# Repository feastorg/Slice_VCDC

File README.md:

# Current & Voltage Reader Slice

Current and voltage reader slice for AC and DC supplies.

## Introduction

[Short introduction on the project.]

## Usage

[Explain how to use the project. Include examples and screenshots if applicable.]

## Documentation

Please refer to the [docs](/docs) for more info.

---

<div align="center">
  
</div>

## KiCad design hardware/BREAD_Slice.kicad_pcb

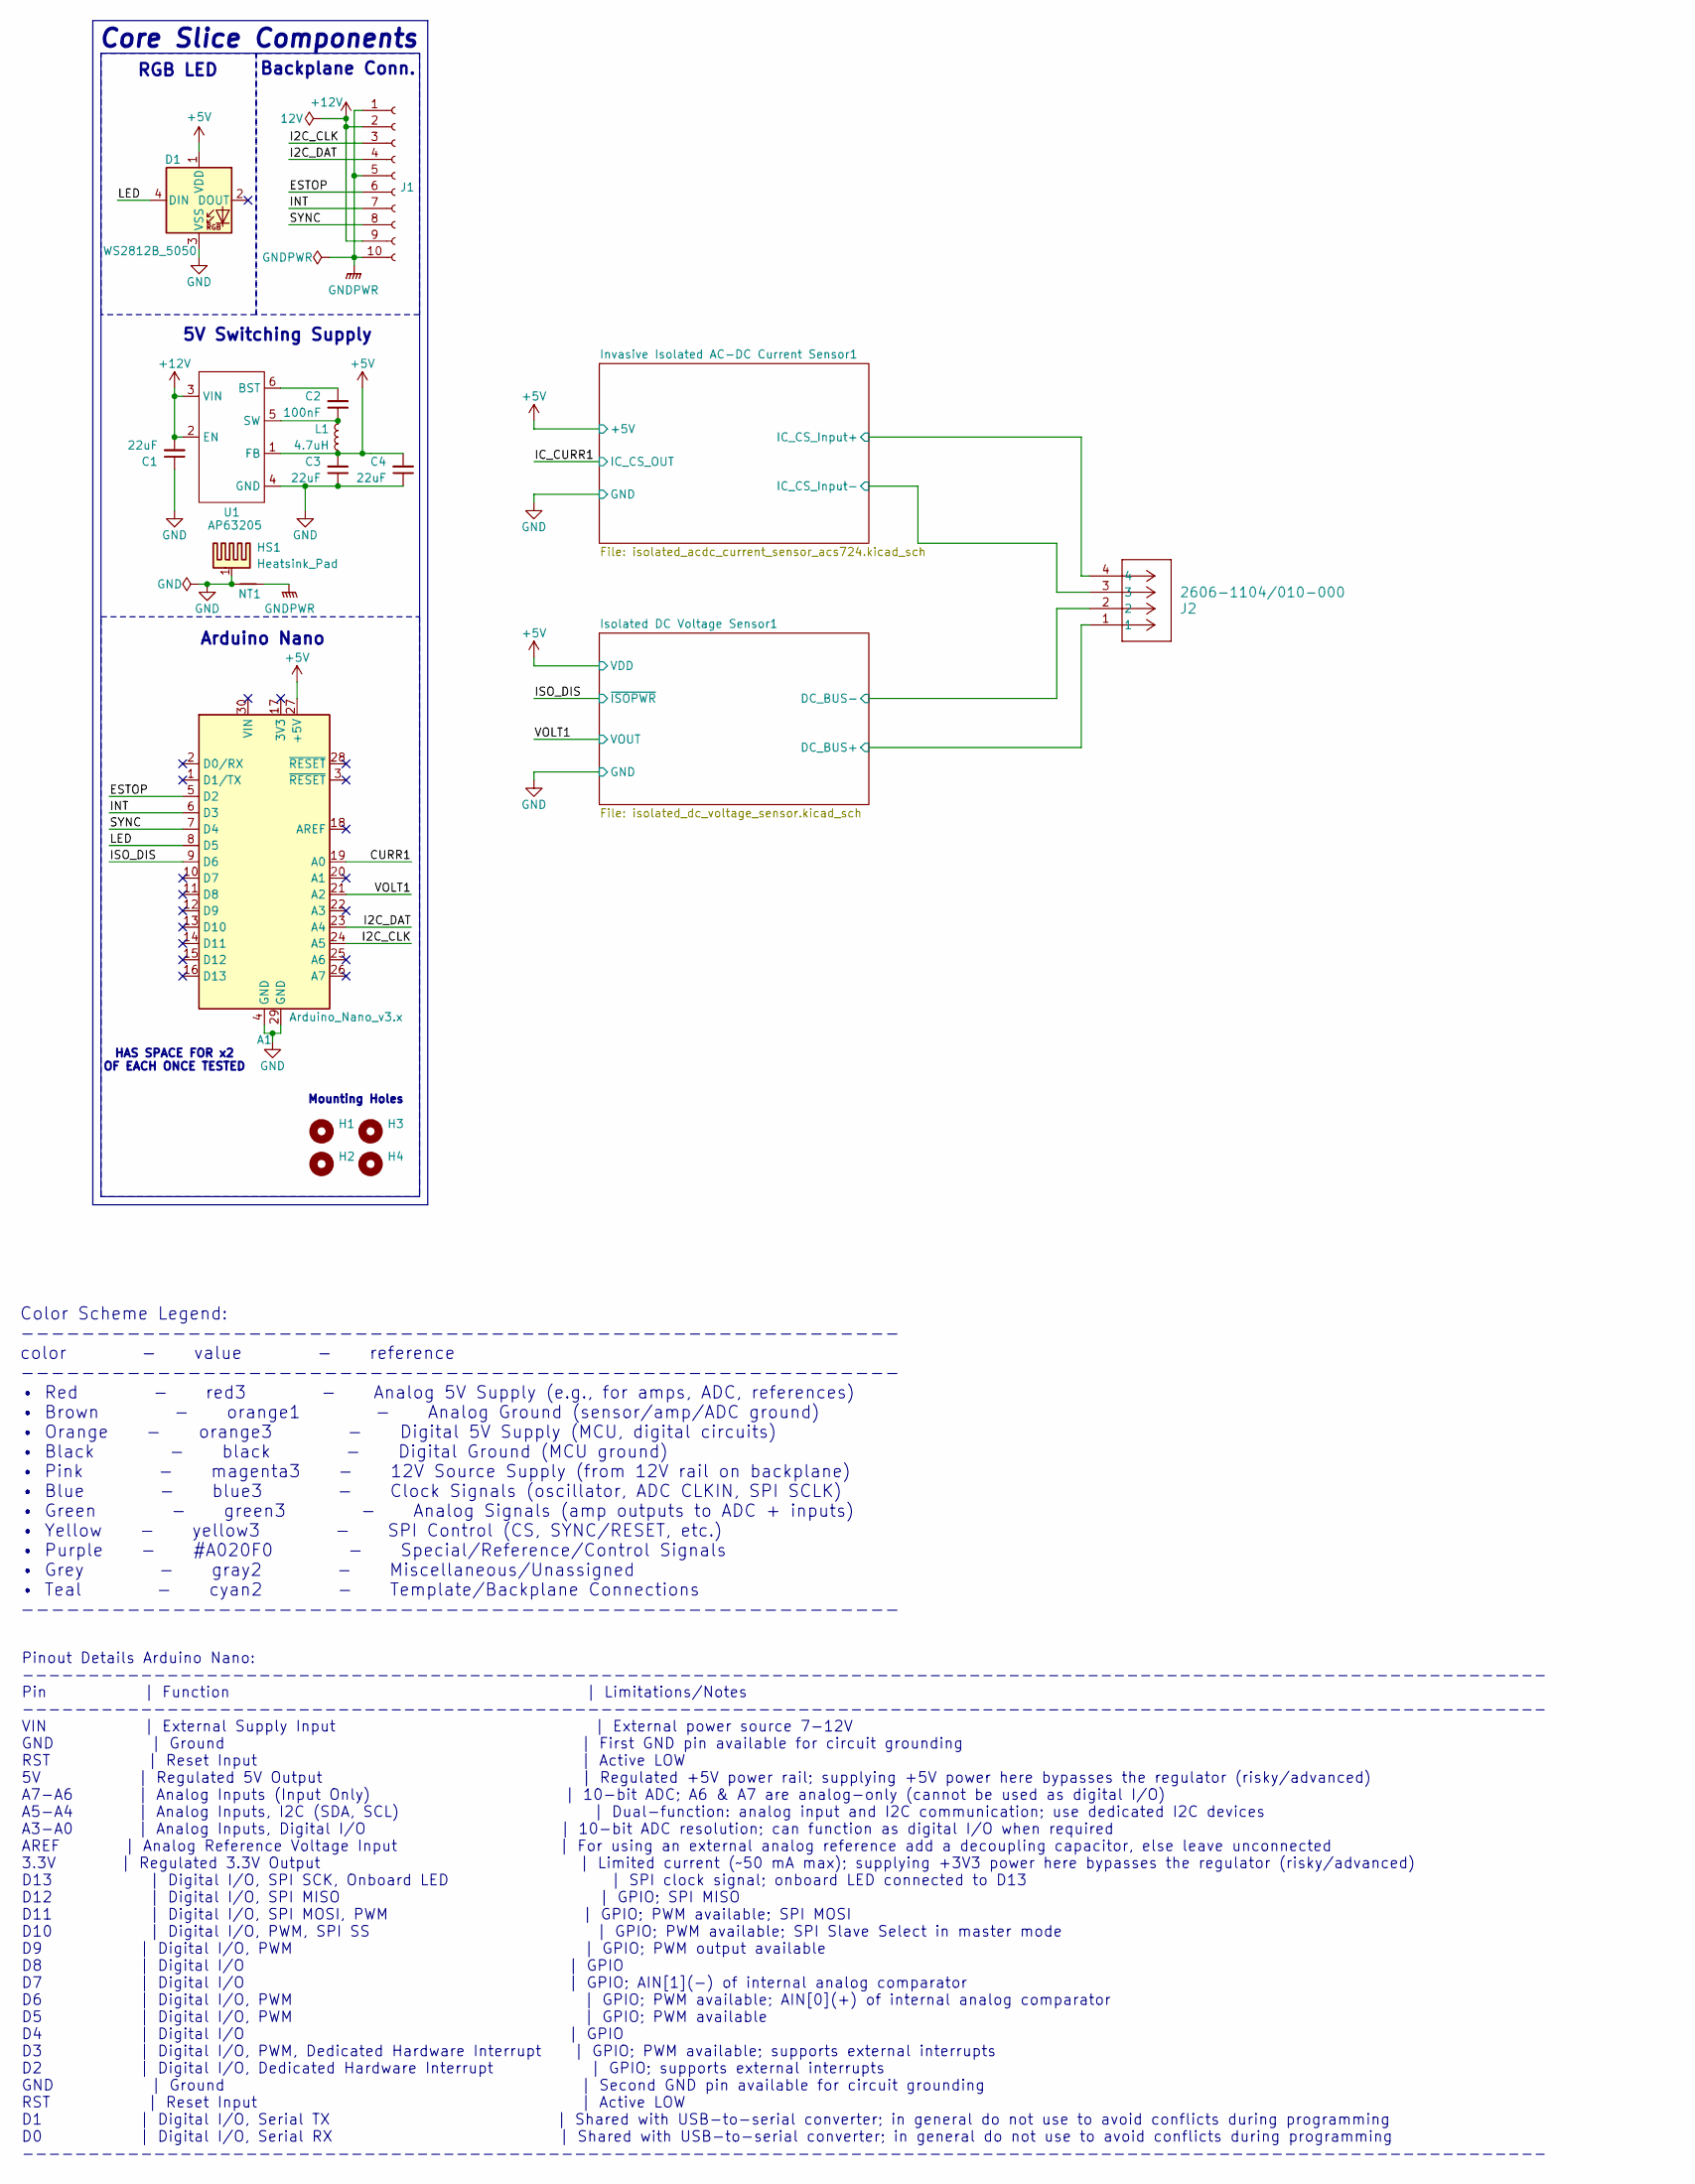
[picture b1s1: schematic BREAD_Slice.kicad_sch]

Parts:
A1: Arduino_Nano_v3.x; Arduino_Nano
C1, C3, C4: 22uF; C_1206_3216Metric
C2: 100nF; C_1206_3216Metric
D1: WS2812B_5050; WS2812-5050-4PIN
H1, H2, H3, H4: MountingHole; MountingHole_5mm
HS1: Heatsink_Pad; Thermal_Pad
J1: Conn_01x10_Female; PinSocket_1x10_P2.54mm_Horizontal
J2: 2606-1104/010-000; CONN4_2606-1104&slash_010-000_WAG
L1: 4.7uH; L_1210_3225Metric
NT1: NetTie_2; NetTie-2_SMD_Pad2.0mm
U1: AP63205; TSOT-23-6

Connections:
+5V: A1.27 (+5V), C3.2, C4.2, D1.1 (VDD), L1.2, U1.1 (FB); also elsewhere on the board
+12V: C1.2, J1.2, J1.9, U1.2 (EN), U1.3 (VIN)
/CURR1: A1.19 (A0)
/ESTOP: A1.5 (D2), J1.6
/I2C_CLK: A1.24 (A5), J1.3
/I2C_DAT: A1.23 (A4), J1.4
/INT: A1.6 (D3), J1.7
/ISO_DIS: A1.9 (D6); also elsewhere on the board
/Invasive Isolated AC-DC Current Sensor1/IC_CS_Input+: J2.4; also elsewhere on the board
/Invasive Isolated AC-DC Current Sensor1/IC_CS_Input-: J2.3; also elsewhere on the board
/Isolated DC Voltage Sensor1/DC_BUS+: J2.1; also elsewhere on the board
/Isolated DC Voltage Sensor1/DC_BUS-: J2.2; also elsewhere on the board
/LED: A1.8 (D5), D1.4 (DIN)
/SYNC: A1.7 (D4), J1.8
/VOLT1: A1.21 (A2); also elsewhere on the board
GND: A1.4 (GND), A1.29 (GND), C1.1, C3.1, C4.1, D1.3 (VSS), HS1.1, NT1.1, U1.4 (GND); also elsewhere on the board
GNDPWR: J1.1, J1.5, J1.10, NT1.2
unnamed: C2.2, U1.6 (BST)
unnamed: C2.1, L1.1, U1.5 (SW)

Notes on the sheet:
5V Switching Supply
HAS SPACE FOR x2 OF EACH ONCE TESTED
Pinout Details Arduino Nano: -------------------------------------------------------------------------------------------------------------------- Pin | Function | Limitations/Notes -------------------------------------------------------------------------------------------------------------------- V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
RGB LED
Color Scheme Legend: ---------------------------------------------------------- color - value - reference ---------------------------------------------------------- • Red - red3 - Analog 5V Supply (e.g., for amps, ADC, references) • Brown - orange1 - Analog Ground (sensor/amp/ADC ground) • Orange -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
Core Slice Components
Arduino Nano
Mounting Holes
Backplane Conn.

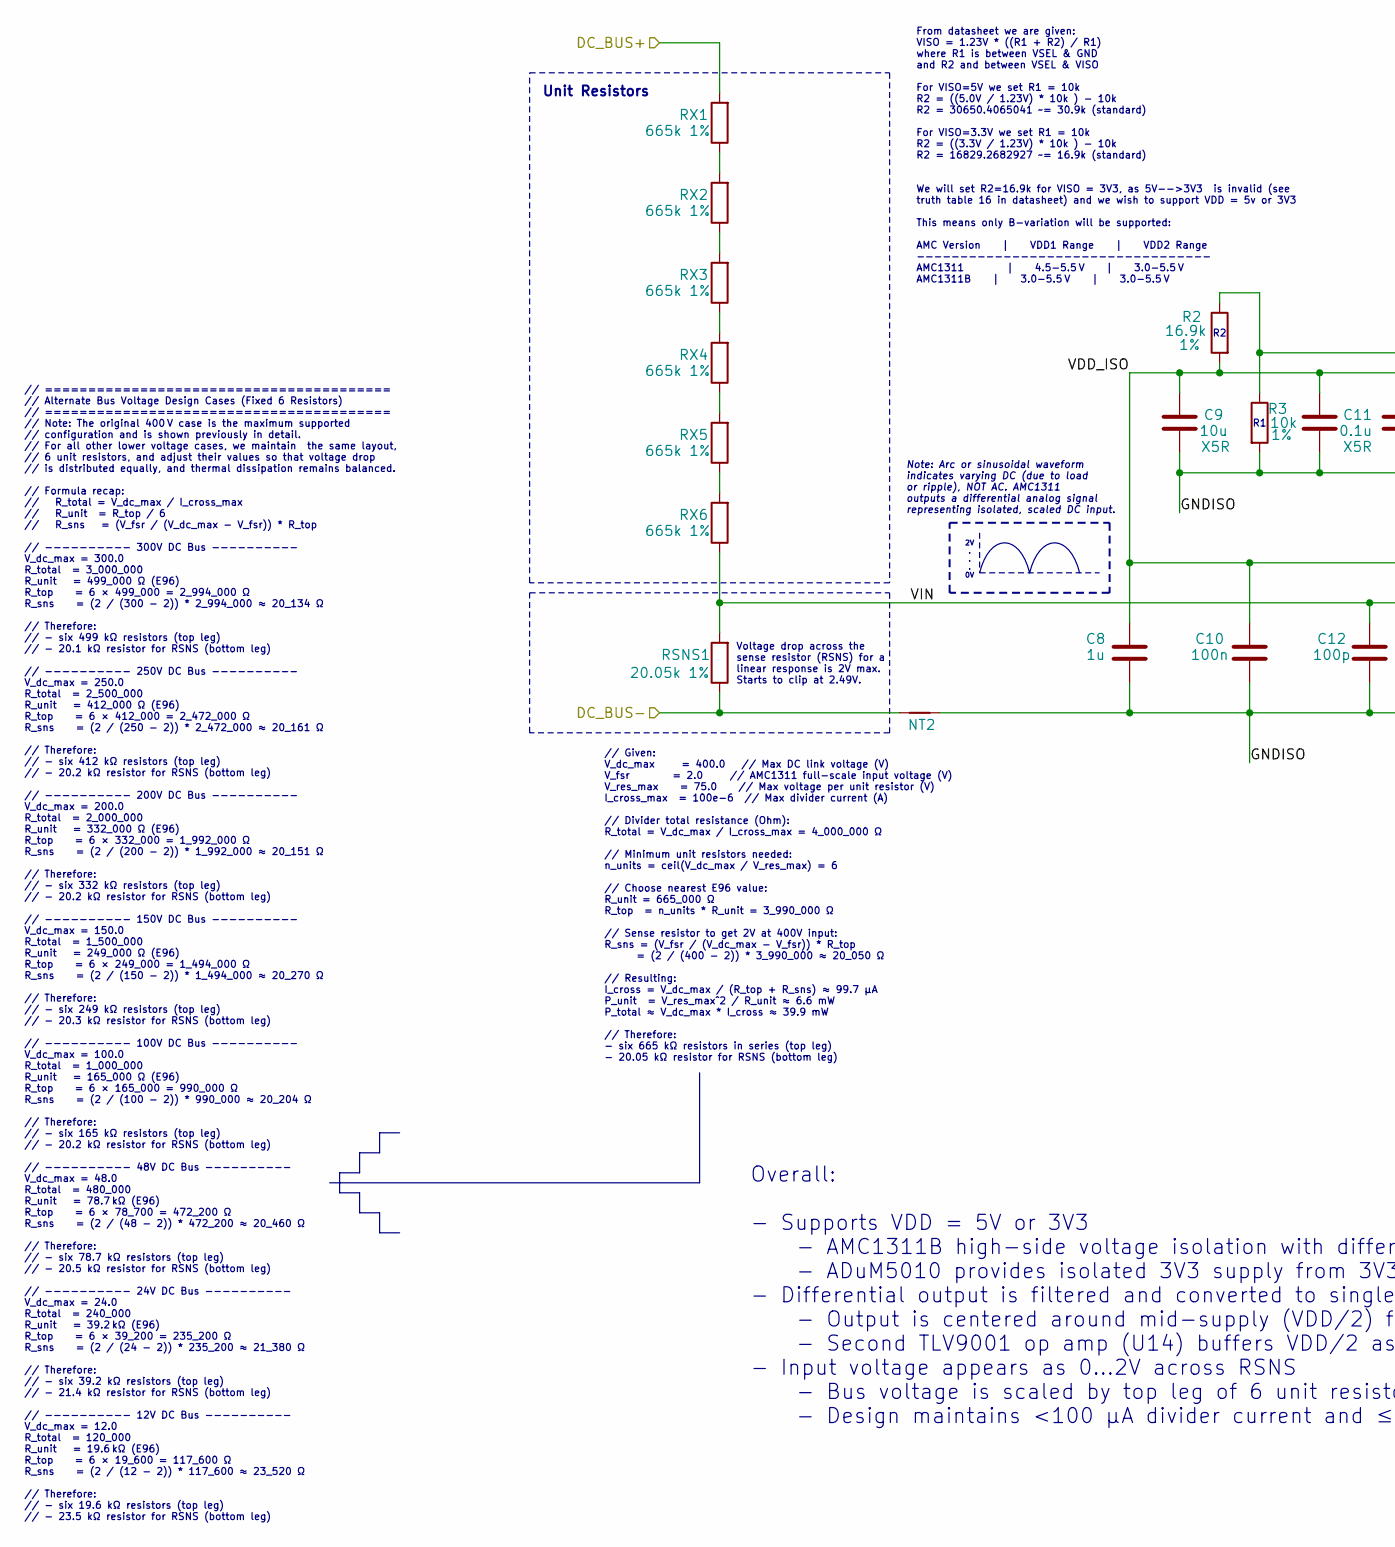
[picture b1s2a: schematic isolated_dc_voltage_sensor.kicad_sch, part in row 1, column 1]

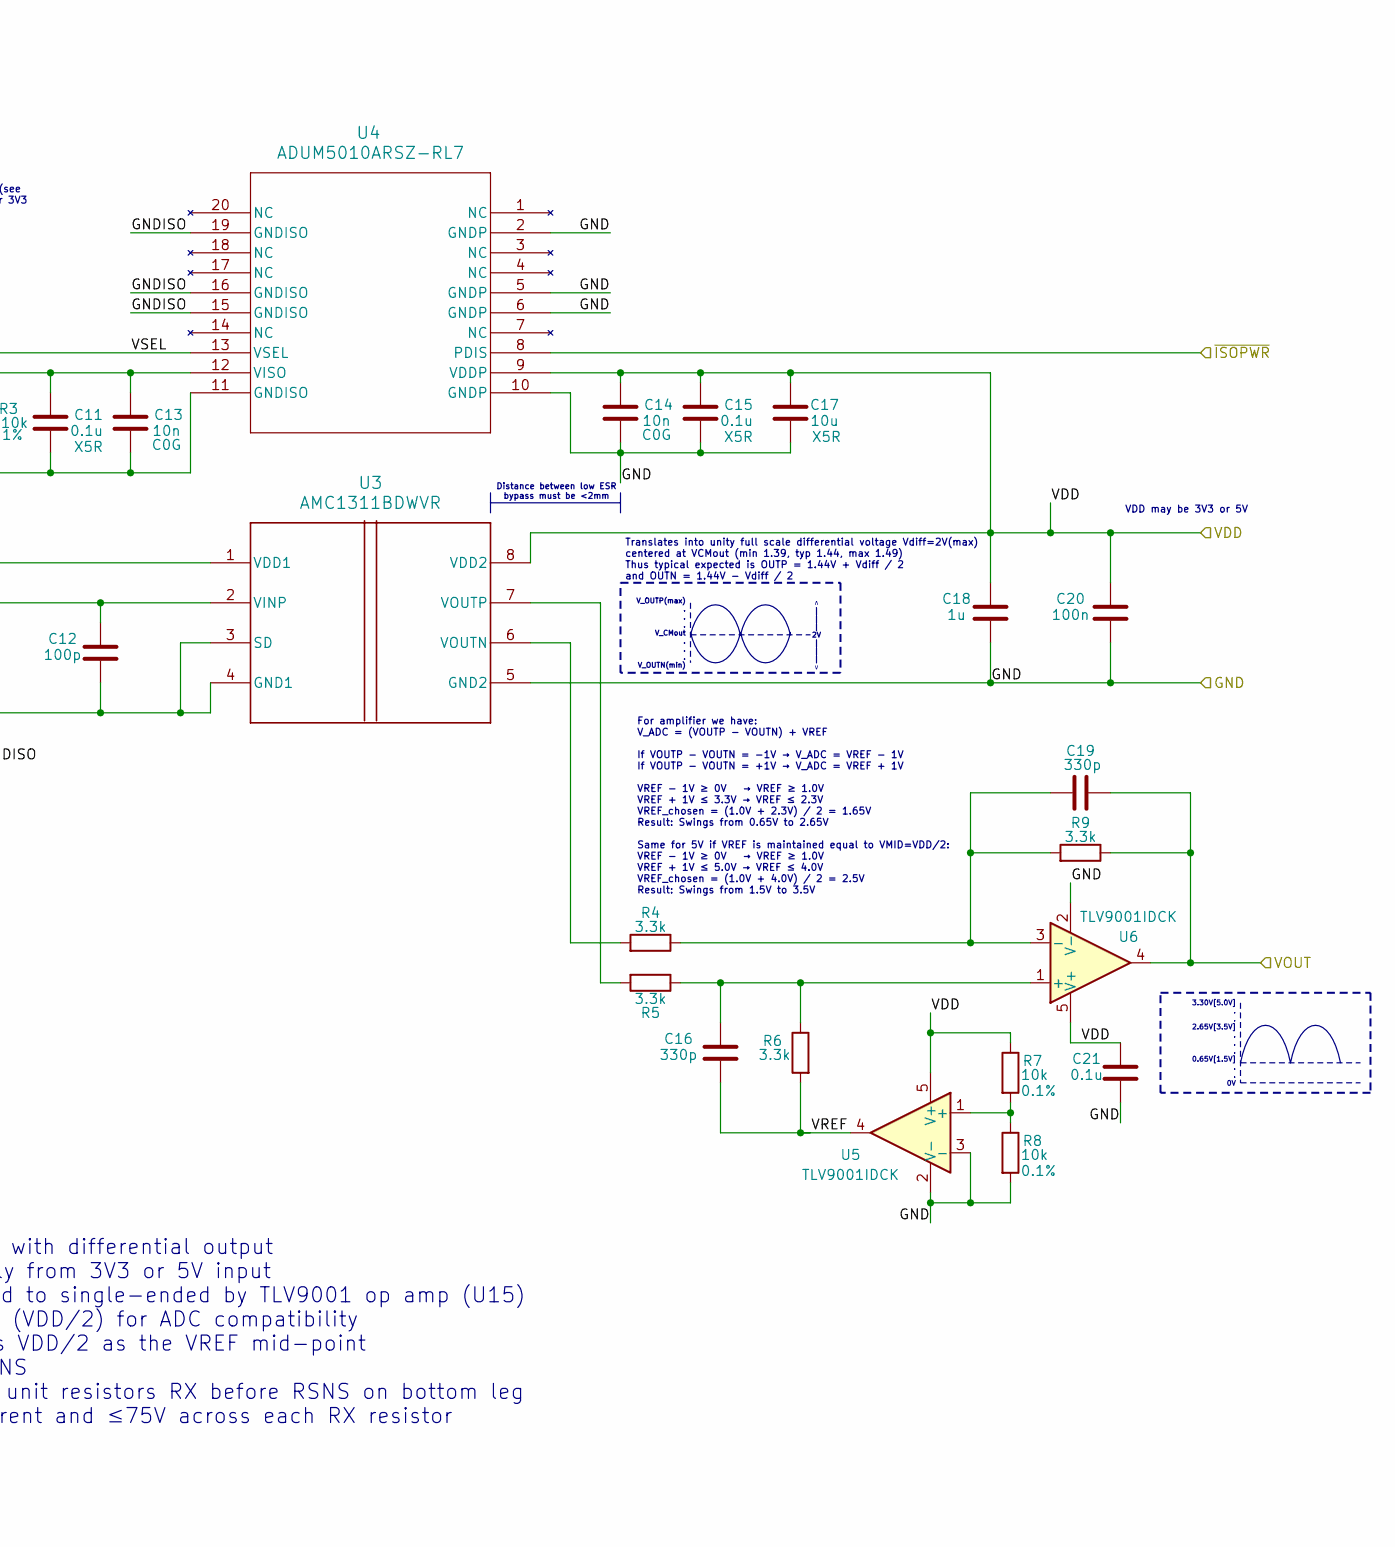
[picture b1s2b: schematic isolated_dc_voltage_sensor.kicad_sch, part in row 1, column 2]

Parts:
C8: 1u; C_0603_1608Metric_Pad1.08x0.95mm_HandSolder
C9, C17: 10u; C_0603_1608Metric_Pad1.08x0.95mm_HandSolder
C10: 100n; C_0603_1608Metric_Pad1.08x0.95mm_HandSolder
C11, C15: 0.1u; C_0603_1608Metric_Pad1.08x0.95mm_HandSolder
C12: 100p; C_0603_1608Metric_Pad1.08x0.95mm_HandSolder
C13, C14: 10n; C_0603_1608Metric_Pad1.08x0.95mm_HandSolder
C16, C19: 330p; C_0805_2012Metric_Pad1.18x1.45mm_HandSolder
C18: 1u; C_0805_2012Metric_Pad1.18x1.45mm_HandSolder
C20: 100n; C_0805_2012Metric_Pad1.18x1.45mm_HandSolder
C21: 0.1u; C_0805_2012Metric_Pad1.18x1.45mm_HandSolder
NT2: NetTie_2; NetTie-2_SMD_Pad0.5mm
R2: 16.9k; R_0603_1608Metric_Pad0.98x0.95mm_HandSolder
R3: 10k; R_0603_1608Metric_Pad0.98x0.95mm_HandSolder
R4, R5, R6, R9: 3.3k; R_0805_2012Metric_Pad1.20x1.40mm_HandSolder
R7, R8: 10k; R_0805_2012Metric_Pad1.20x1.40mm_HandSolder
RSNS1: 20.05k 1%; R_1206_3216Metric_Pad1.30x1.75mm_HandSolder
RX1, RX2, RX3, RX4, RX5, RX6: 665k 1%; R_1206_3216Metric_Pad1.30x1.75mm_HandSolder
U3: AMC1311BDWVR; DWV0008A
U4: ADUM5010ARSZ-RL7; RS_20_ADI
U5, U6: TLV9001IDCK; SOT-353_SC-70-5

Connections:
+5V: C14.2, C15.2, C17.2, C18.2, C20.2, C21.2, R7.1, U3.8 (VDD2), U4.9 (VDDP), U5.5 (V+), U6.5 (V+); also elsewhere on the board
/ISO_DIS: U4.8 (PDIS); also elsewhere on the board
/Isolated DC Voltage Sensor1/DC_BUS+: RX1.2; also elsewhere on the board
/Isolated DC Voltage Sensor1/DC_BUS-: NT2.1, RSNS1.1; also elsewhere on the board
/Isolated DC Voltage Sensor1/GNDISO: C8.1, C9.1, C10.1, C11.1, C12.1, C13.1, NT2.2, R3.2, U3.3 (SD), U3.4 (GND1), U4.11 (GNDISO), U4.15 (GNDISO), U4.16 (GNDISO), U4.19 (GNDISO)
/Isolated DC Voltage Sensor1/VDD_ISO: C8.2, C9.2, C10.2, C11.2, C13.2, R2.2, U3.1 (VDD1), U4.12 (VISO)
/Isolated DC Voltage Sensor1/VIN: C12.2, RSNS1.2, RX6.1, U3.2 (VINP)
/Isolated DC Voltage Sensor1/VREF: C16.1, R6.2, U5.4
/Isolated DC Voltage Sensor1/VSEL: R2.1, R3.1, U4.13 (VSEL)
/VOLT1: C19.2, R9.1, U6.4; also elsewhere on the board
GND: C14.1, C15.1, C17.1, C18.1, C20.1, C21.1, R8.2, U3.5 (GND2), U4.2 (GNDP), U4.5 (GNDP), U4.6 (GNDP), U4.10 (GNDP), U5.2 (V-), U5.3 (-), U6.2 (V-); also elsewhere on the board
unnamed: RX1.1, RX2.2
unnamed: RX2.1, RX3.2
unnamed: RX3.1, RX4.2
unnamed: RX4.1, RX5.2
unnamed: RX5.1, RX6.2
unnamed: R4.2, U3.6 (VOUTN)
unnamed: R5.2, U3.7 (VOUTP)
unnamed: R7.2, R8.1, U5.1 (+)
unnamed: C16.2, R5.1, R6.1, U6.1 (+)
unnamed: C19.1, R4.1, R9.2, U6.3 (-)

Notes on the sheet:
VDD may be 3V3 or 5V
// Given: V_dc_max = 400.0 // Max DC link voltage (V) V_fsr = 2.0 // AMC1311 full-scale input voltage (V) V_res_max = 75.0 // Max voltage per unit resistor (V) I_cross_max = 100e-6 // Max divider current (A) // Divider total resistance (Ohm): R_total = V_dc_max / I_cross_max = 4_000_000 Ω // Minimu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
// ======================================== // Alternate Bus Voltage Design Cases (Fixed 6 Resistors) // ======================================== // Note: The original 400 V case is the maximum supported // configuration and is shown previously in detail. // For all other lower voltage cases, we ma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
∧ | | | 2V | | | ∨
Voltage drop across the sense resistor (RSNS) for a linear response is 2V max. Starts to clip at 2.49V.
Overall: - Supports VDD = 5V or 3V3 - AMC1311B high-side voltage isolation with differential output - ADuM5010 provides isolated 3V3 supply from 3V3 or 5V input - Differential output is filtered and converted to single-ended by TLV9001 op amp (U15) - Output is centered around mid-supply (VDD/2) for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
2V . . . 0V
3.30V[5.0V] . . 2.65V[3.5V] . . . 0.65V[1.5V] . . 0V
Unit Resistors
Distance between low ESR bypass must be <2mm
For amplifier we have: V_ADC = (VOUTP - VOUTN) + VREF If VOUTP - VOUTN = -1V → V_ADC = VREF - 1V If VOUTP - VOUTN = +1V → V_ADC = VREF + 1V VREF - 1V ≥ 0V → VREF ≥ 1.0V VREF + 1V ≤ 3.3V → VREF ≤ 2.3V VREF_chosen = (1.0V + 2.3V) / 2 = 1.65V Result: Swings from 0.65V to 2.65V Same for 5V if VREF is m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
From datasheet we are given: VISO = 1.23V * ((R1 + R2) / R1) where R1 is between VSEL & GND and R2 and between VSEL & VISO For VISO=5V we set R1 = 10k R2 = ((5.0V / 1.23V) * 10k ) - 10k R2 = 30650.4065041 ~= 30.9k (standard) For VISO=3.3V we set R1 = 10k R2 = ((3.3V / 1.23V) * 10k ) - 10k R2 = 1682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
Translates into unity full scale differential voltage Vdiff=2V(max) centered at VCMout (min 1.39, typ 1.44, max 1.49) Thus typical expected is OUTP = 1.44V + Vdiff / 2 and OUTN = 1.44V - Vdiff / 2
V_OUTP(max) . . . V_CMout . . . V_OUTN(min)
Note: Arc or sinusoidal waveform indicates varying DC (due to load or ripple), NOT AC. AMC1311 outputs a differential analog signal representing isolated, scaled DC input.

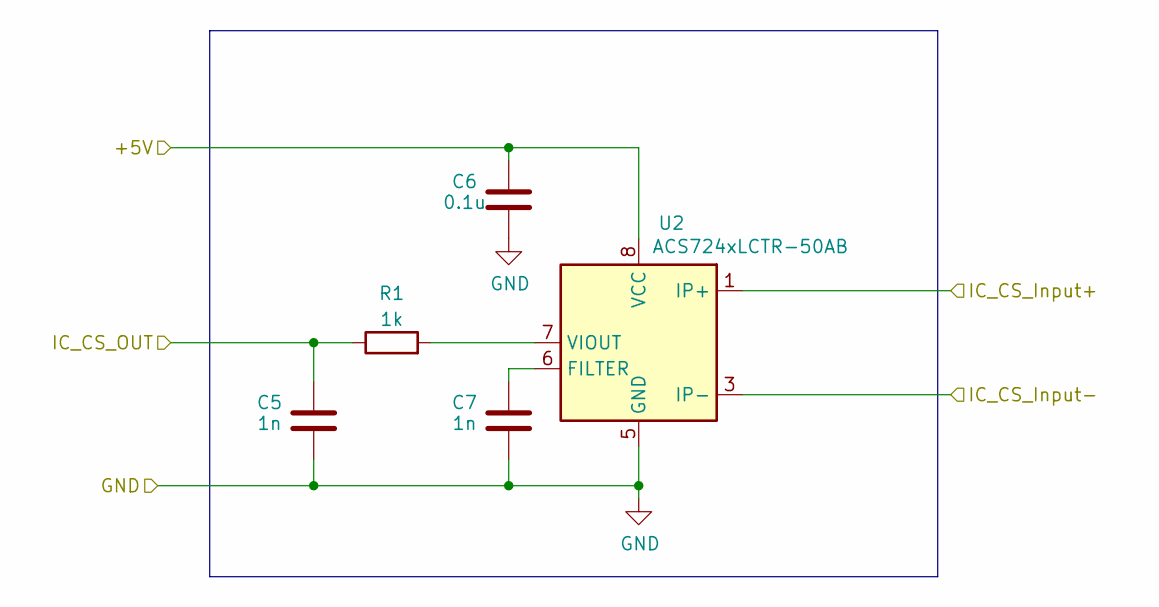
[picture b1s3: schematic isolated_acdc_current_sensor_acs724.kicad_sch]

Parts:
C5, C7: 1n; C_0805_2012Metric_Pad1.18x1.45mm_HandSolder
C6: 0.1u; C_0805_2012Metric_Pad1.18x1.45mm_HandSolder
R1: 1k; R_0805_2012Metric_Pad1.20x1.40mm_HandSolder
U2: ACS724xLCTR-50AB; SOIC-8_3.9x4.9mm_P1.27mm

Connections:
+5V: C6.2, U2.8 (VCC); also elsewhere on the board
/IC_CURR1: C5.2, R1.1
/Invasive Isolated AC-DC Current Sensor1/IC_CS_Input+: U2.1 (IP+), U2.2 (IP+); also elsewhere on the board
/Invasive Isolated AC-DC Current Sensor1/IC_CS_Input-: U2.3 (IP-), U2.4 (IP-); also elsewhere on the board
GND: C5.1, C6.1, C7.1, U2.5 (GND); also elsewhere on the board
unnamed: C7.2, U2.6 (FILTER)
unnamed: R1.2, U2.7 (VIOUT)

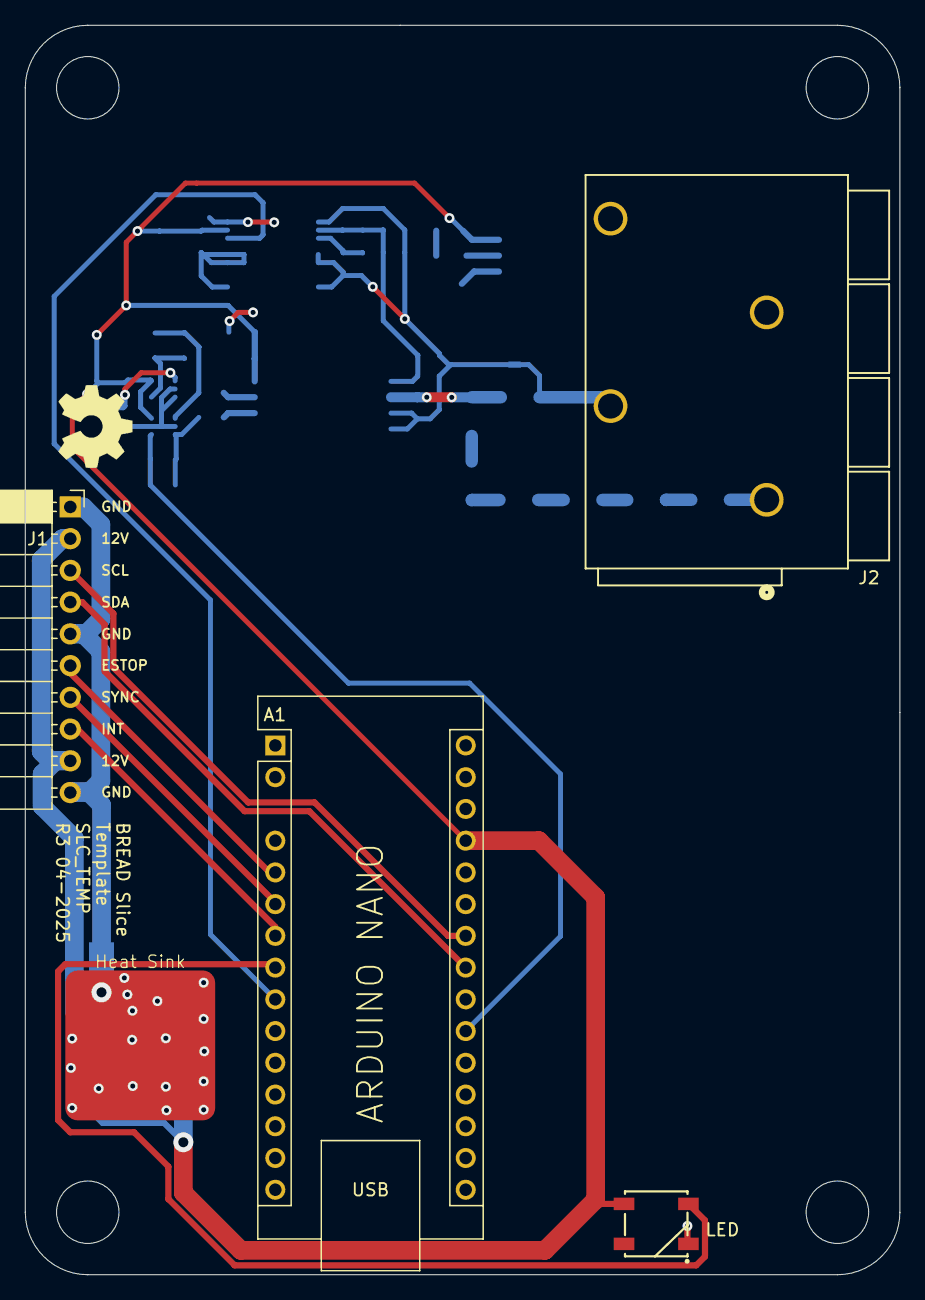
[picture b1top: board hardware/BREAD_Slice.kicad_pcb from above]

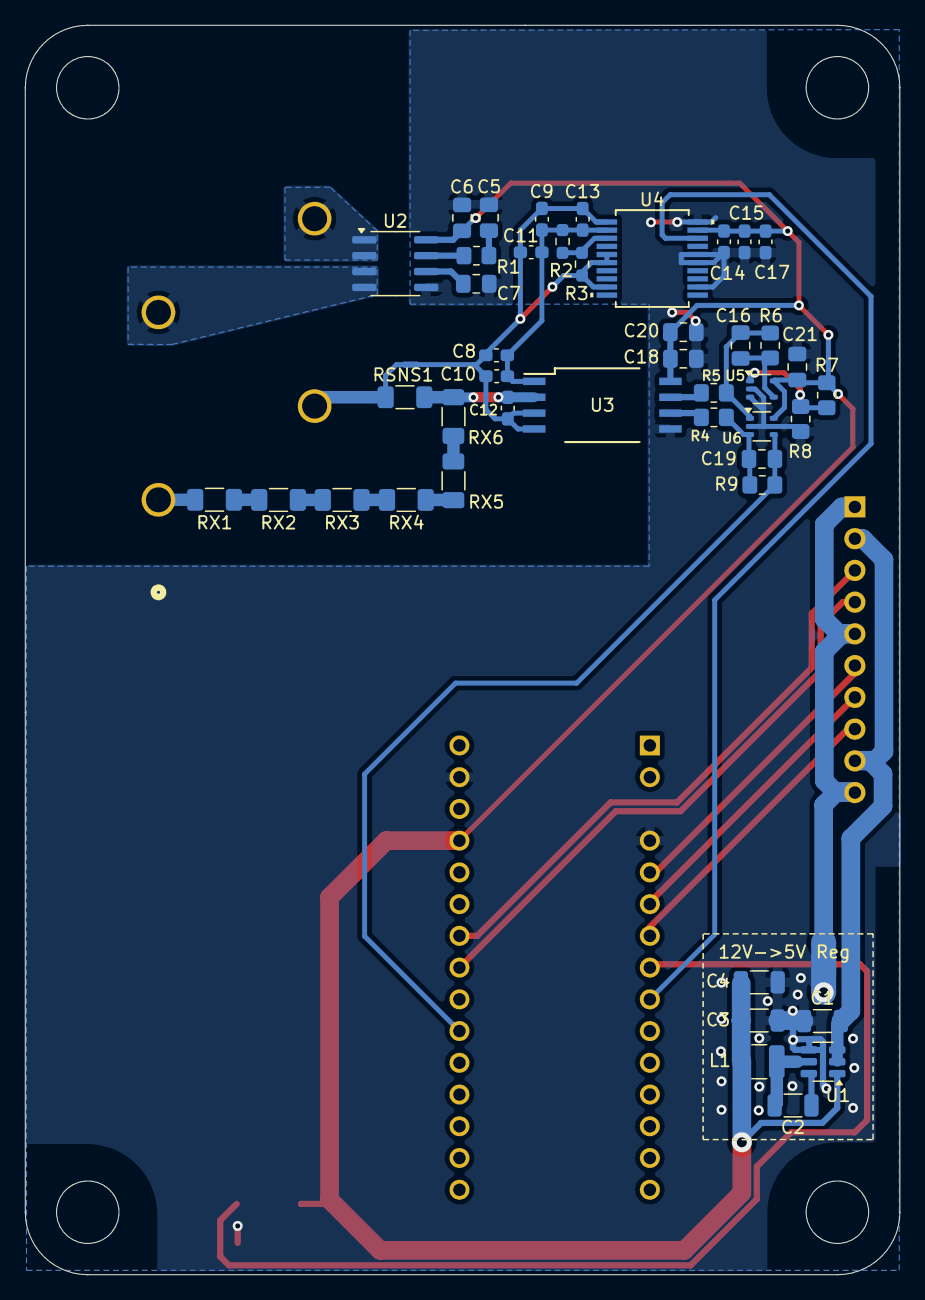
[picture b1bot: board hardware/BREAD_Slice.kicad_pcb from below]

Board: 2 copper layers, 70.0 x 100.0 mm, 56 parts (46 on the bottom side), 36 nets.

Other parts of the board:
Logo1: Logo_Open_Hardware_Small; OSHW-Symbol_6.7x6mm_SilkScreen

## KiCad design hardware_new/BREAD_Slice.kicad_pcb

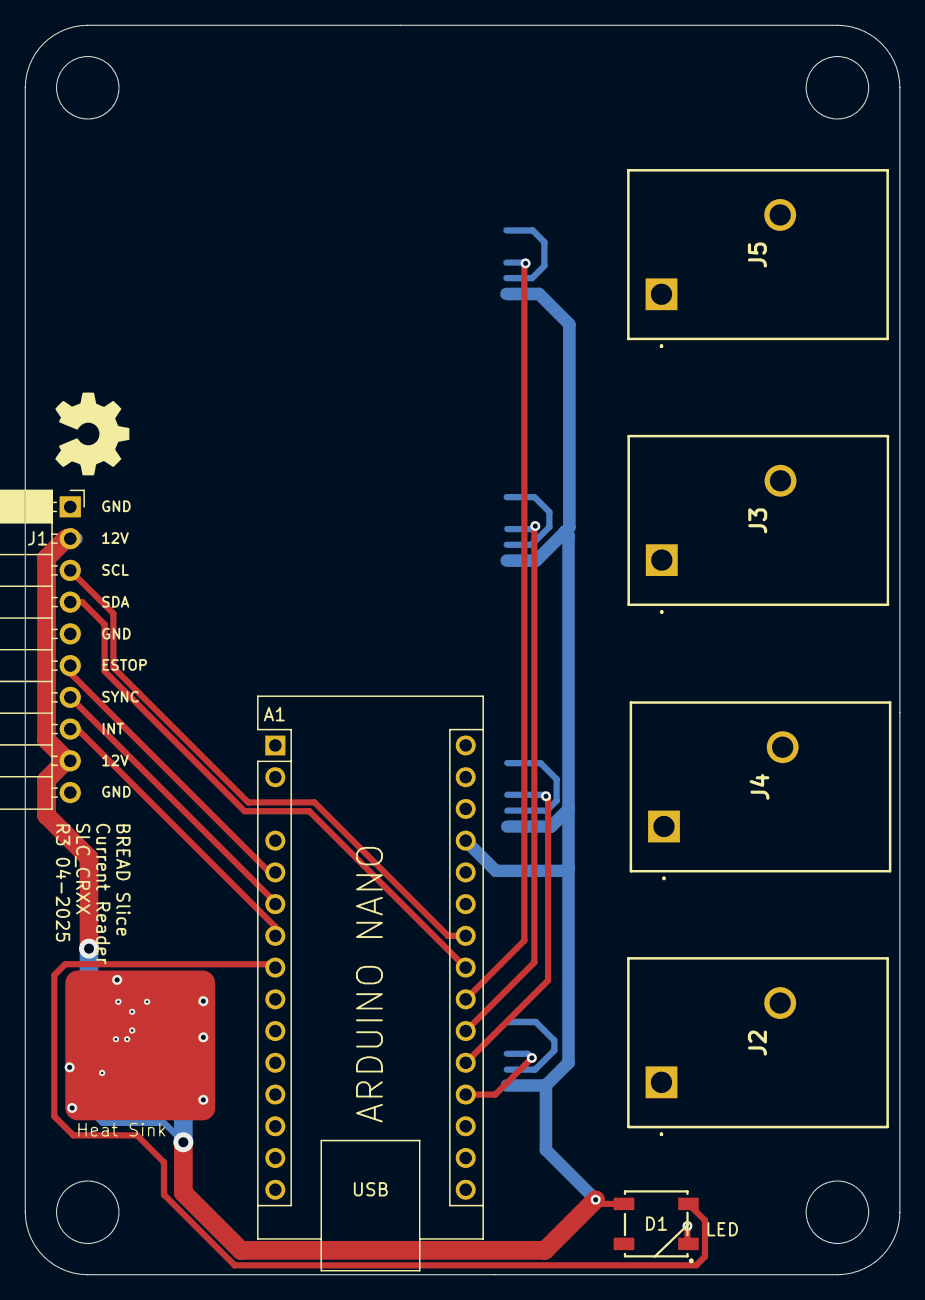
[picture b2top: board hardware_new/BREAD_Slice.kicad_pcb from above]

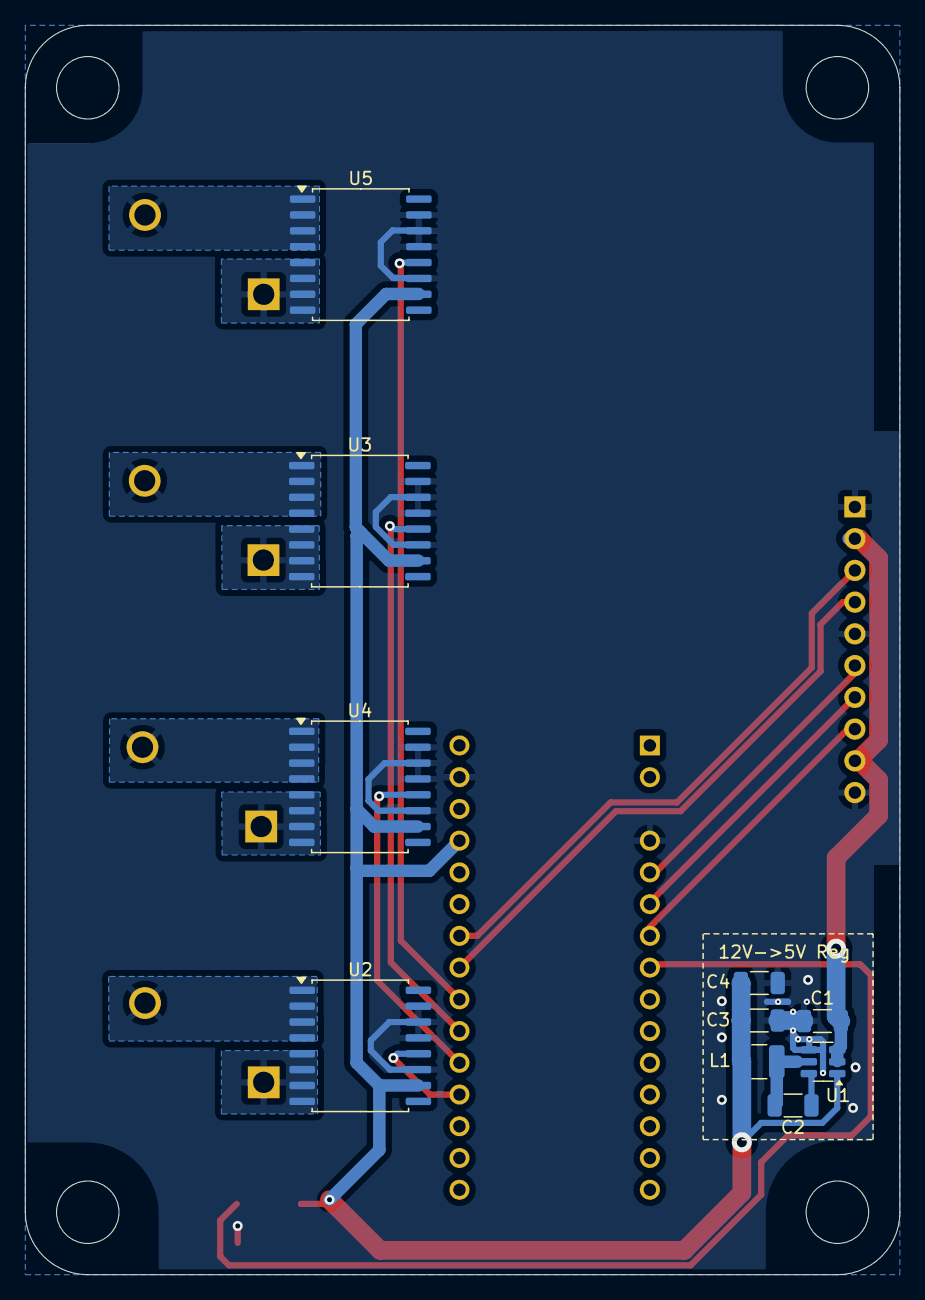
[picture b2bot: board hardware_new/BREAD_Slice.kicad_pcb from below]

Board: 2 copper layers, 70.0 x 100.0 mm, 23 parts (10 on the bottom side), 23 nets.

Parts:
A1: Arduino_Nano_v3.x; Arduino_Nano
C1, C3, C4: 22uF; C_1206_3216Metric
C2: 100nF; C_1206_3216Metric
D1: WS2812B_5050; WS2812-5050-4PIN
H1, H2, H3, H4: MountingHole; MountingHole_5mm
HS1: Heatsink_Pad; Thermal Pad
J1: Conn_01x10_Female; PinSocket_1x10_P2.54mm_Horizontal
J2, J3, J4, J5: Screw_Terminal_01x02; Pheonix Conn Term TDPT 4 2-SP-6,35-ZB
L1: 4.7uH; L_1210_3225Metric
Logo1: Logo_Open_Hardware_Small; OSHW-Symbol_6.7x6mm_SilkScreen
U1: TSOT-23-6
U2, U3, U4, U5: ACS723xMATR-10AB; SOIC-16W_7.5x10.3mm_P1.27mm

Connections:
+5V: A1.27 (+5V), C3.2, C4.2, D1.1 (VDD), L1.2, U1.1 (FB), U2.10 (VCC), U3.10 (VCC), U4.10 (VCC), U5.10 (VCC)
+12V: C1.2, J1.2, J1.9, U1.2 (EN), U1.3 (VIN)
/CURR1: A1.19 (A0), U2.12 (VIOUT)
/CURR2: A1.20 (A1), U4.12 (VIOUT)
/CURR3: A1.21 (A2), U3.12 (VIOUT)
/CURR4: A1.22 (A3), U5.12 (VIOUT)
/E_STOP: A1.5 (D2), J1.6
/I2C_CLK: A1.24 (A5), J1.3
/I2C_DAT: A1.23 (A4), J1.4
/INT: A1.6 (D3), J1.7
/LED: A1.8 (D5), D1.4 (DIN)
/SYNC: A1.7 (D4), J1.8
GND: A1.4 (GND), A1.29 (GND), C1.1, C3.1, C4.1, D1.3 (VSS), HS1.1, J1.1, J1.5, J1.10, U1.4 (GND), U2.11 (NC), U2.13 (BW_SEL), U2.14 (NC), U2.15 (GND), U3.11 (NC), U3.13 (BW_SEL), U3.14 (NC), U3.15 (GND), U4.11 (NC), U4.13 (BW_SEL), U4.14 (NC), U4.15 (GND), U5.11 (NC), U5.13 (BW_SEL), U5.14 (NC), U5.15 (GND)
unnamed: J2.1, U2.5 (IP-), U2.6 (IP-), U2.7 (IP-), U2.8 (IP-)
unnamed: J2.2, U2.1 (IP+), U2.2 (IP+), U2.3 (IP+), U2.4 (IP+)
unnamed: J3.1, U3.5 (IP-), U3.6 (IP-), U3.7 (IP-), U3.8 (IP-)
unnamed: J3.2, U3.1 (IP+), U3.2 (IP+), U3.3 (IP+), U3.4 (IP+)
unnamed: J4.1, U4.5 (IP-), U4.6 (IP-), U4.7 (IP-), U4.8 (IP-)
unnamed: J4.2, U4.1 (IP+), U4.2 (IP+), U4.3 (IP+), U4.4 (IP+)
unnamed: J5.1, U5.5 (IP-), U5.6 (IP-), U5.7 (IP-), U5.8 (IP-)
unnamed: J5.2, U5.1 (IP+), U5.2 (IP+), U5.3 (IP+), U5.4 (IP+)
unnamed: C2.2, U1.6 (BST)
unnamed: C2.1, L1.1, U1.5 (SW)

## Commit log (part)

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2024-08-30 updated fabrication outputs
2024-09-10 update repo
2024-09-27 updated silkscreen info
2025-03-31 updated to latest template
2025-03-31 removed old
2025-04-05 added updated CRXX and schem for CRVS iteration
2025-04-18 updated board, last push before change to CRVR
2025-04-19 final schematic done before split to ac dc
2025-04-19 initial commit after split of ac and dc
2025-04-19 minor tweaks
2025-05-05 completed board
2025-09-24 add press fit terms
2026-05-20 Add slice.yaml manifest (schema v1.0)
2026-05-24 Add KiBot/docs pipeline
2026-05-24 Update TODO with CI results
2026-05-24 Standardize TODO.md with Pass 1/Pass 2 structure
